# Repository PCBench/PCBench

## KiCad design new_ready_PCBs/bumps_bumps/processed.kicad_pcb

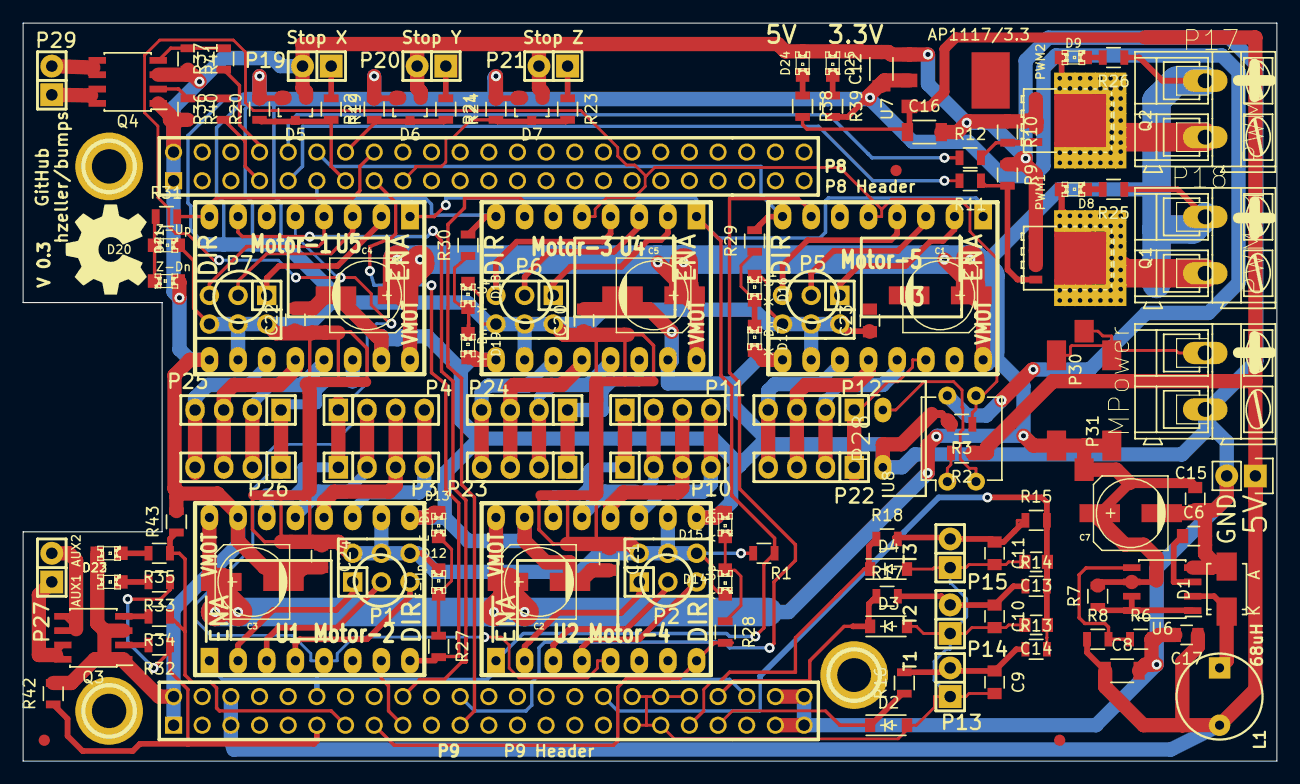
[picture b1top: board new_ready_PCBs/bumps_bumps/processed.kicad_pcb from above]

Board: 2 copper layers, 111.1 x 65.4 mm, 134 parts (0 on the bottom side), 101 nets.

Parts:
C1, C2, C3, C4, C5, C7: 100u; c_elec_6.3x7.7
C6: 110p; C_0805
C8: 100u; C_1206
C9, C10, C11, C14: 10u; C_0805
C12, C16: 22u; C_1206
C13, C15, C17, C20, C21, C22, C23, C24: 100n; C_0805
D1: STPS130A; Diode-SMA_Standard
D2, D3, D4: 1.8V; SOD-123
D5, D6, D7: BAT54S; SOT-23
D8: PWM1; LED-0805
D9: PWM2; LED-0805
D12: E-Up; LED-0805
D13: E-Dn; LED-0805
D14: A-Up; LED-0805
D15: A-Dn; LED-0805
D16: X-Up; LED-0805
D17: X-Dn; LED-0805
D18: Y-Up; LED-0805
D19: Y-Dn; LED-0805
D20: Z-Up; LED-0805
D21: Z-Dn; LED-0805
D22: AUX1; LED-0805
D23: AUX2; LED-0805
D24: 5V; LED-0805
D25: 3.3V; LED-0805
L1: 68uH; INDUCTOR_V
M1, M2, M3: CONN_1; 1pin
P1, P2, P5, P6, P7: DIL6; Pin_Header_Straight_2x03
P3, P4: Mot-E; Pin_Header_Straight_1x04
P8: P8 Header; PIN_ARRAY_23X2
P9: P9 Header; PIN_ARRAY_23X2
P10, P11: Mot-A; Pin_Header_Straight_1x04
P12, P22: Mot-X; Pin_Header_Straight_1x04
P13: T1; Pin_Header_Straight_1x02
P14: T2; Pin_Header_Straight_1x02
P15, P32: T3; Pin_Header_Straight_1x02
P16: MPower; AK300-2
P17: PWM-2; AK300-2
P18: PWM-1; AK300-2
P19: END-X; Pin_Header_Straight_1x02
P20: END-Y; Pin_Header_Straight_1x02
P21: END-Z; Pin_Header_Straight_1x02
P23, P24: Mot-Y; Pin_Header_Straight_1x04
P25, P26: Mot-Z; Pin_Header_Straight_1x04
P27: Aux; Pin_Header_Straight_1x02
P28: KillSwitch; WideHeader
P29: PWM; Pin_Header_Straight_1x02
P30, P31: CONN_01X01; FuseBlade
Q1, Q2: BUK9Y15-60E; SOT-669_LFPAK_ThermalVias-1
Q3, Q4: FDS9926A; SOIC-8_3.9x4.9mm_Pitch1.27mm
R1, R3, R13, R14, R15, R20, R22, R24: 4k7; R_0805
R2: 330; R_0805
R6, R27, R28, R29, R30, R31, R33, R35, R38, R39: 1k; R_0805
R7: 0R3; R_0805
R8: 3k; R_0805
R9, R10, R40, R41, R42, R43: 100k; R_0805
R11, R12, R16, R17, R18, R19, R21, R23, R32, R34, R36, R37: 68; R_0805
R25, R26: 2k2; R_0805
U1: Motor-2; POLOLU
U2: Motor-4; POLOLU
U3: Motor-5; POLOLU
U4: Motor-3; POLOLU
U5: Motor-1; POLOLU
U6: MC34063; SOIC-8_3.9x4.9mm_Pitch1.27mm
U7: AP1117/3.3; SOT-223-3
U8: PC817; DIP-4_W7.62mm

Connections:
AGND: C9.2, C10.2, C11.2, C13.2, C14.2, D2.2, D3.2, D4.2, P9.33, P9.34, P9.35, P9.36, P9.38, P13.1, P14.1, P15.1
AUX_1: P9.11, R32.1, R33.1, R42.1
AUX_2: P9.13, R34.1, R35.1, R43.1
DIR_A: P9.15, R28.2, U2.8
DIR_E: P8.15, R27.2, U1.8
DIR_X: P8.12, R29.2, U3.8
DIR_Y: P8.11, R30.2, U4.8
DIR_Z: P8.16, R31.2, U5.8
END_X: D5.3, P8.13, R19.2, R20.1
END_Y: D6.3, P8.14, R21.2, R22.1
END_Z: D7.3, P8.17, R23.2, R24.1
GND: C2.2, C3.2, C4.2, C5.2, C6.2, C7.2, C8.2, C12.2, C15.2, C16.2, C17.2, C20.2, C21.2, C22.2, C24.2, D1.2, D5.1, D6.1, D7.1, D13.1, D15.1, D17.1, D19.1, D21.1, D22.1, D23.1, D24.1, D25.1, P8.1, P8.2, P9.1, P9.2, P9.43, P9.44, P9.45, P9.46, P16.2, P19.2, P20.2, P21.2, P28.1, P32.2, Q1.1, Q1.2, Q1.3, Q2.1, Q2.2, Q2.3, Q3.1, Q3.3, Q4.1, Q4.3, R3.2, R6.2, R9.1, R10.1, R40.2, R41.2, R42.2, R43.2, U1.9, U1.15, U2.9, U2.15, U3.9, U4.9, U4.15, U5.9, U5.15, U6.4, U7.1
unnamed: C6.1, U6.3
unnamed: C9.1, P13.2, R13.1, R16.2
unnamed: C10.1, P14.2, R14.1, R17.2
unnamed: C11.1, P15.2, R15.1, R18.2
unnamed: D1.1, L1.1, U6.2
unnamed: D8.1, P18.2, Q1.5
unnamed: D8.2, R25.2
unnamed: D9.1, P17.2, Q2.5
unnamed: D9.2, R26.2
unnamed: D12.1, D13.2, R27.1
unnamed: D14.1, D15.2, R28.1
unnamed: D16.1, D17.2, R29.1
unnamed: D18.1, D19.2, R30.1
unnamed: D20.1, D21.2, R31.1
unnamed: D22.2, R33.2
unnamed: D23.2, R35.2
unnamed: D24.2, R38.1
unnamed: D25.2, R39.1
unnamed: P1.1, U1.2
unnamed: P1.2, U1.3
unnamed: P1.3, U1.4
unnamed: P2.1, U2.2
unnamed: P2.2, U2.3
unnamed: P2.3, U2.4
unnamed: P3.1, P4.1, U1.14
unnamed: P3.2, P4.2, U1.13
unnamed: P3.3, P4.3, U1.12
unnamed: P3.4, P4.4, U1.11
unnamed: P5.1, U3.2
unnamed: P5.2, U3.3
unnamed: P5.3, U3.4
unnamed: P6.1, U4.2
unnamed: P6.2, U4.3
unnamed: P6.3, U4.4
unnamed: P7.1, U5.2
unnamed: P7.2, U5.3
unnamed: P7.3, U5.4
unnamed: P10.1, P11.1, U2.14
unnamed: P10.2, P11.2, U2.13
unnamed: P10.3, P11.3, U2.12
unnamed: P10.4, P11.4, U2.11
unnamed: P12.1, P22.1, U3.14
unnamed: P12.2, P22.2, U3.13
unnamed: P12.3, P22.3, U3.12
unnamed: P12.4, P22.4, U3.11
unnamed: P16.1, P30.1
unnamed: P19.1, R19.1
unnamed: P20.1, R21.1
unnamed: P21.1, R23.1
unnamed: P23.1, P24.1, U4.14
unnamed: P23.2, P24.2, U4.13
unnamed: P23.3, P24.3, U4.12
unnamed: P23.4, P24.4, U4.11
unnamed: P25.1, P26.1, U5.14
unnamed: P25.2, P26.2, U5.13
unnamed: P25.3, P26.3, U5.12
unnamed: P25.4, P26.4, U5.11
unnamed: P27.1, Q3.7, Q3.8
unnamed: P27.2, Q3.5, Q3.6
unnamed: P28.2, U8.2
unnamed: P29.1, Q4.7, Q4.8
unnamed: P29.2, Q4.5, Q4.6
unnamed: Q1.4, R9.2, R11.1
unnamed: Q2.4, R10.2, R12.2
unnamed: Q3.2, R32.2
unnamed: Q3.4, R34.2
unnamed: Q4.2, R36.2, R40.1
unnamed: Q4.4, R37.2, R41.1
unnamed: R2.2, U8.1
unnamed: R6.1, R8.2, U6.5
unnamed: R7.1, U6.1, U6.7, U6.8
PWM_1: P8.9, R11.2
PWM_2: P8.10, R12.1
PWM_3: P8.7, R36.1
PWM_4: P8.8, R37.1
STEP_A: P9.42, U2.7
STEP_E: P9.17, U1.7
STEP_X: P9.22, U3.7
STEP_Y: P9.21, U4.7
STEP_Z: P9.18, U5.7
TEMP_1: D2.1, P9.39, R16.1
TEMP_2: D3.1, P9.40, R17.1
TEMP_3: D4.1, P9.37, R18.1
VDD_3V3: C12.1, C20.1, C21.1, C22.1, C23.1, C24.1, D5.2, D6.2, D7.2, D12.2, D14.2, D16.2, D18.2, D20.2, P1.4, P1.5, P1.6, P2.4, P2.5, P2.6, P5.4, P5.5, P5.6, P6.4, P6.5, P6.6, P7.4, P7.5, P7.6, R1.2, R20.2, R22.2, R24.2, R39.2, U1.10, U2.10, U3.10, U4.10, U5.10, U7.2, U8.4
VDD_5V: C8.1, C16.1, C17.1, L1.2, P9.5, P9.6, P32.1, R2.1, R8.1, R38.2, U7.3
VDD_ADC: C13.1, C14.1, P9.32, R13.2, R14.2, R15.2
VMOT: C1.1, C2.1, C3.1, C4.1, C5.1, C7.1, C15.1, P17.1, P18.1, P31.1, R7.2, R25.1, R26.1, U1.16, U2.16, U3.16, U4.16, U5.16, U6.6
~EN: P9.12, R1.1, U1.1, U2.1, U3.1, U4.1, U5.1
~EStop: R3.1, U1.5, U2.5, U3.5, U4.5, U5.5, U8.3

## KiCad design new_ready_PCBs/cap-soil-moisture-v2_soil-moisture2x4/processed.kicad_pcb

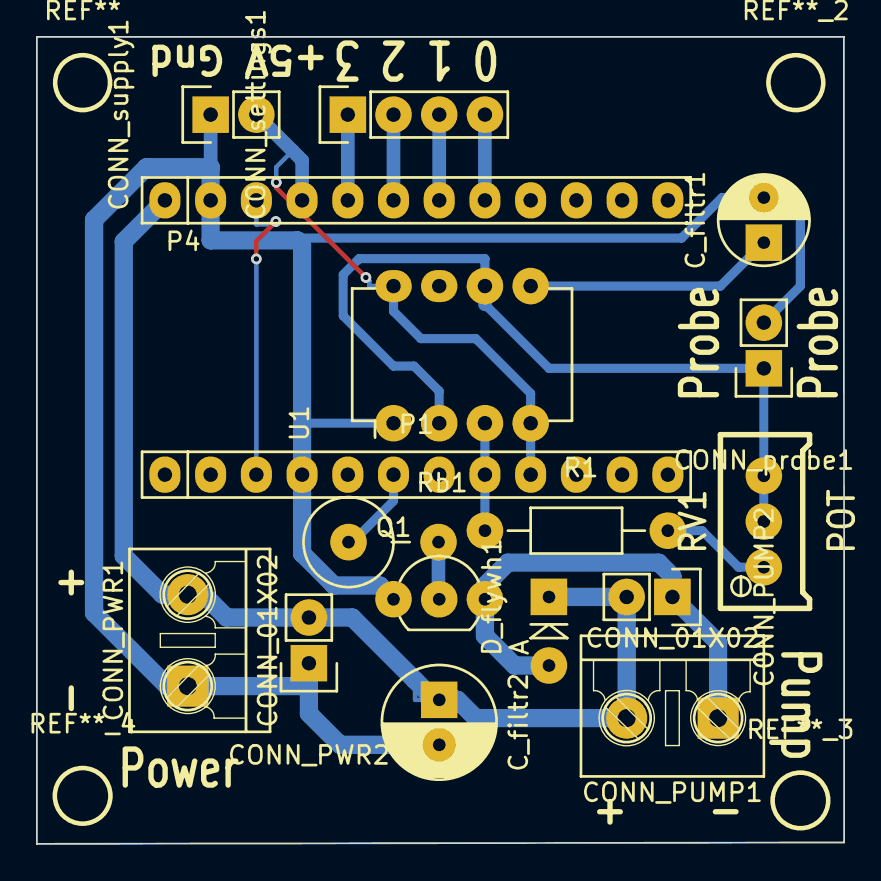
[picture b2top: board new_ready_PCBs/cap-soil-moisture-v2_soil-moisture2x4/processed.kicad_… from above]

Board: 2 copper layers, 44.8 x 44.8 mm, 17 parts (0 on the bottom side), 15 nets.

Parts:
CONN_PUMP1: CONN_01X02; KF301-2P-B
CONN_PUMP2: CONN_01X02; Pin_Header_Straight_1x02
CONN_PWR1: CONN_01X02; KF301-2P-B
CONN_PWR2: CONN_01X02; Pin_Header_Straight_1x02
CONN_probe1: CONN_01X02; Pin_Header_Straight_1x02
CONN_settings1: CONN_01X04; Pin_Header_Straight_1x04
CONN_supply1: CONN_01X02; Pin_Header_Straight_1x02
C_filtr1: CP1; C_Radial_D5_L6_P2.5
C_filtr2: CP1; C_Radial_D6.3_L11.2_P2.5
D_flywh1: D_Small; Diode_DO-41_SOD81_Vertical_AnodeUp
P1: Digital; Socket_Strip_Arduino_1x12
P4: Analog; Socket_Strip_Arduino_1x12
Q1: 2N2222; TO-92_Inline_Wide
R1: R; Resistor_Horizontal_RM10mm
RV1: POT; RV-bline
Rb1: 470R; Resistor_Vertical_RM5mm
U1: LM555N; DIP-8_W7.62mm

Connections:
+12V: CONN_PUMP1.2, CONN_PUMP2.2, CONN_PWR1.2, CONN_PWR2.2, C_filtr2.1, D_flywh1.1, P4.1
/3(**): P1.6, Rb1.1
/5(**): P1.8, R1.1, U1.3
/A0: CONN_settings1.4, P4.8
/A1: CONN_settings1.3, P4.7
/A2: CONN_settings1.2, P4.6
/A3: CONN_settings1.1, P4.5
/Reset: P1.3, P4.3
GND: CONN_PWR1.1, CONN_PWR2.1, CONN_probe1.2, CONN_supply1.1, C_filtr1.2, C_filtr2.2, P1.4, P4.2, Q1.1, U1.1
unnamed: CONN_PUMP1.1, CONN_PUMP2.1, D_flywh1.2, Q1.3
unnamed: CONN_probe1.1, RV1.2, RV1.3, U1.2, U1.6
unnamed: C_filtr1.1, U1.5
unnamed: Q1.2, Rb1.2
unnamed: R1.2, RV1.1
VCC: CONN_supply1.2, P1.9, P4.4, U1.4, U1.8

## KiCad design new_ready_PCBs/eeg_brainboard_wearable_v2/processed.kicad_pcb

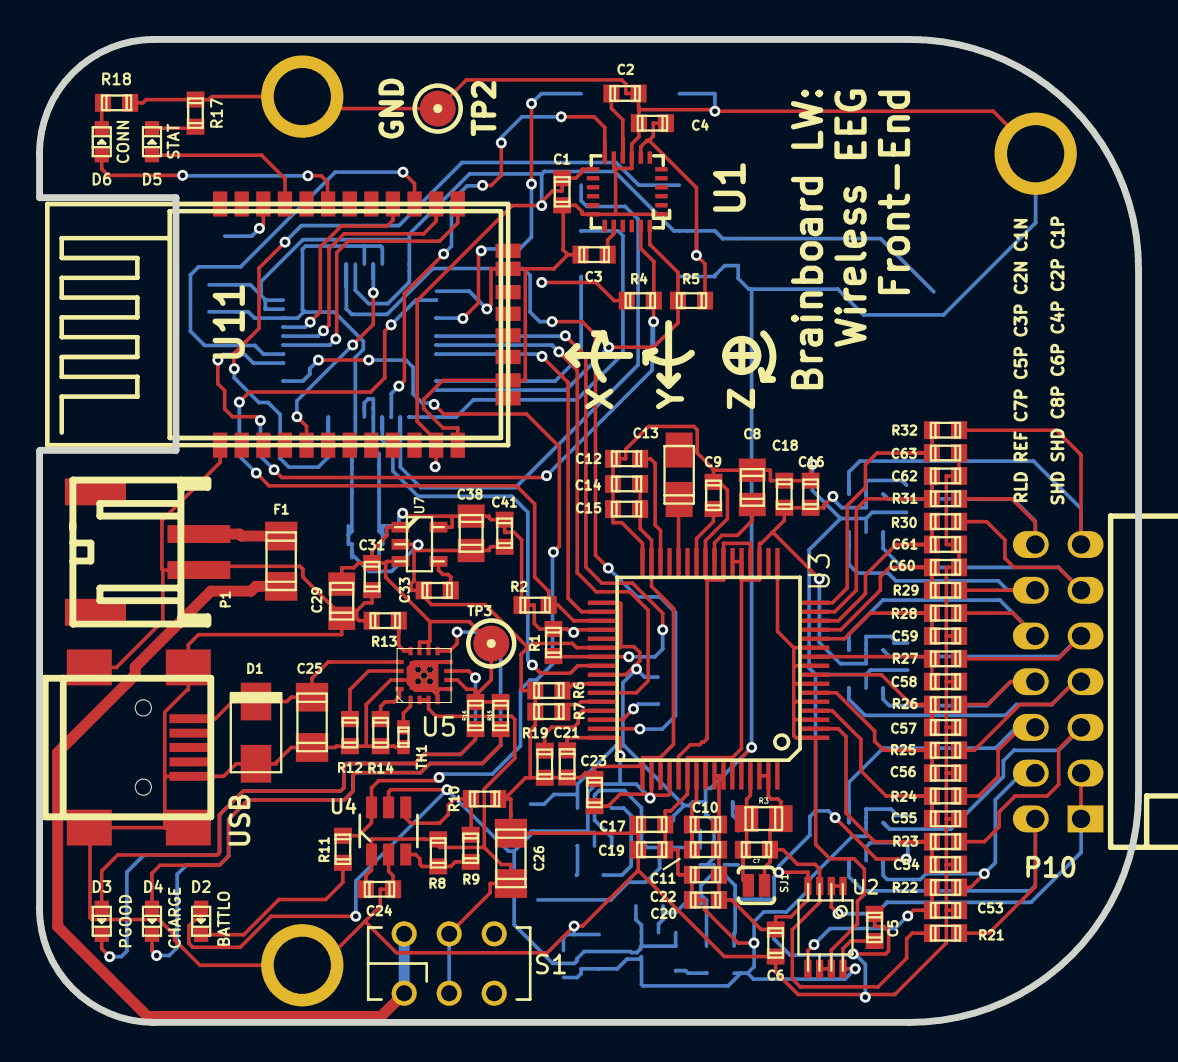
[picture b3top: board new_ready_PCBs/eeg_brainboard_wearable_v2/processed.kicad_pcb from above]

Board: 4 copper layers, 61.1 x 54.6 mm, 134 parts (0 on the bottom side), 89 nets.

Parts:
C1, C2, C5, C6, C11, C15, C18, C19, C22, C23, C24, C31, C42, C43, C45, C47, C48, C49, C50, C51, C52: 0.1uF; c_0603
C3: 2.2nF; c_0603
C4, C33, C34, C35: 0.01uF; c_0603
C7: 1nF; c_0603
C8, C29, C36, C37, C38, C46: 10uF; c_0805
C9, C10, C12, C14, C16, C17, C20, C21, C27, C28, C30, C32: 1uF; c_0603
C13: 100uF; c_tant_S
C25: 2.2uF; c_1206
C26: 10uF; c_1206
C39, C40, C41, C44: 2.2uF; c_0603
C53, C54, C55, C56, C57, C58, C59, C60, C61, C62, C63: 4.7nF; c_0603
CON1: USB; USB_MINI_B
D1: SMAJ7.0A; do214ac
D2: BATTLO; Led_0603
D3: PGOOD; Led_0603
D4: CHARGE; Led_0603
D5: STAT; Led_0603
D6: CONN; Led_0603
F1: PTC 500mA; r_1206
MTG1, MTG2, MTG3: MHOLE; BBB_MHOLE
P1: JST; s2b-ph-sm4-tb
P8: CONN_5X2; bb02-hp10
P10: CONN_14; pin_socket_7x2-90
R1, R2: 10K; r_0603
R3: 499K,0.1%; r_0805
R4, R5: 4.7k; r_0603
R6, R7, R19, R20: 10k; r_0603
R8: 562k; r_0603
R9: 51.1k; r_0603
R10: 383k; r_0603
R11, R15, R16, R17, R18: 2.2k; r_0603
R12: 52.3k; r_0603
R13: 1.18k; r_0603
R14: 4.42k; r_0603
R21, R22, R23, R24, R25, R26, R27, R28, R29, R30, R31, R32: 4.99K; r_0603
S1: DPDT; JS202011AQN
SJ1: NO BIAS FILT; SparkFun-Passives-SJ_2S-NO
TH1: NTC 10K; r_0402
TP1, TP2: GND; testpoint_2mm
TP3: PREREG; testpoint_2mm
TP4: -3V3; testpoint_2mm
TP5: +2V5; testpoint_2mm
TP6: -2V5; testpoint_2mm
TP7: BTRST; testpoint_2mm
TP8: 3V3; testpoint_2mm
U1: MPU6050; QFN24-4x4
U2: OPA2376; msoic-8
U3: ADS1299; TQFP_64
U4: LTC1998; tsot23-6
U5: BQ24074(T); s-pvqfn-n16-vias
U6: TPS60403; sot23-5
U7: TPS73233; sot23-5
U8: TPS73225; sot23-5
U9: TPS72325; sot23-5
U10: ATUC3L064; -TQFP48
U11: BLUETOOTH-RN42; roving_rn-42
U12, U13, U14: TPD4E001DBV; sot23-6

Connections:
+2.5V: C5.1, C16.1, C17.1, C18.1, C19.1, C20.1, C22.1, C36.1, C39.1, C42.1, C50.1, C51.1, C52.1, TP5.1, U2.8, U3.19, U3.21, U3.22, U3.54, U3.56, U3.59, U8.5, U12.5, U13.5, U14.5
+3.3V: C1.1, C4.1, C21.1, C23.1, C27.1, C32.1, C38.1, C41.1, C43.1, C44.1, C45.1, C46.1, C47.1, C48.1, C49.1, D2.1, P8.4, R1.1, R2.1, R4.1, R5.1, TP8.1, U1.8, U1.13, U3.36, U3.48, U3.50, U3.52, U4.5, U6.2, U7.5, U8.1, U8.3, U10.17, U10.18, U10.34, U10.35, U10.42, U10.48, U11.11
+BATT: C24.1, C26.1, R8.1, S1.2, S1.5, U4.1, U5.2, U5.3
-2.5V: C6.1, C8.1, C9.2, C10.2, C11.2, C12.2, C13.2, C14.1, C15.1, C16.2, C18.2, C20.2, C22.2, C37.1, C40.1, C42.2, C50.2, C51.2, C52.2, TP6.1, U2.4, U3.20, U3.23, U3.25, U3.32, U3.53, U3.57, U3.58, U9.5, U12.2, U13.2, U14.2
-3.3V: C30.1, TP4.1, U6.1, U9.2, U9.3
/BATTLO: R11.1, U4.6, U10.26
/Brainboard AFE/BIASINV: C7.1, R3.2, SJ1.1, U3.61
/Brainboard AFE/SRB1: U2.6, U2.7, U3.1, U3.3, U3.5, U3.7, U3.9, U3.11, U3.17
/Brainboard AFE/VCAP1: C13.1, U3.28
/Brainboard AFE/VCAP2: C12.1, U3.30
/Brainboard AFE/VCAP3: C10.1, C11.1, U3.55
/Brainboard AFE/VCAP4: C9.1, U3.26
/Brainboard AFE/VREFP: C8.2, U3.24
/Brainboard Analog In/BIAS_ELEC: P10.2, R21.1, U14.3
/Brainboard Analog In/CH1ELEC_N: P10.14, R31.1, U12.6
/Brainboard Analog In/CH1ELEC_P: P10.13, R32.1, U12.4
/Brainboard Analog In/CH2ELEC_N: P10.12, R29.1, U12.3
/Brainboard Analog In/CH2ELEC_P: P10.11, R30.1, U12.1
/Brainboard Analog In/CH3ELEC_P: P10.10, R28.1, U13.4
/Brainboard Analog In/CH4ELEC_P: P10.9, R27.1, U13.6
/Brainboard Analog In/CH5ELEC_P: P10.8, R26.1, U13.1
/Brainboard Analog In/CH6ELEC_P: P10.7, R25.1, U13.3
/Brainboard Analog In/CH7ELEC_P: P10.6, R24.1, U14.4
/Brainboard Analog In/CH8ELEC_P: P10.5, R23.1, U14.6
/Brainboard Analog In/REF_ELEC: P10.4, R22.1, U14.1
/Brainboard Bluetooth/FACTORY: TP7.1, U11.22
/Brainboard Bluetooth/STATUS: D6.1, U11.19
/Brainboard Bluetooth/STATUSn: D5.1, U11.21
/Brainboard IMU/CPOUT: C3.1, U1.20
/Brainboard IMU/REGOUT: C2.1, U1.10
/Brainboard MCU/RESET_MCU: P8.6, U10.22
/Brainboard MCU/TCK: P8.1, U10.11
/Brainboard MCU/TDI: P8.9, U10.4
/Brainboard MCU/TDO: P8.3, U10.13
/Brainboard MCU/TMS: P8.5, U10.14
/Brainboard Power/B+: F1.2, P1.1
/Brainboard Power/ILIM: R13.1, U5.12
/Brainboard Power/ISET: R14.1, U5.16
/Brainboard Power/OUT: C29.1, C31.1, R15.1, R16.1, TP3.1, U5.6, U5.10, U5.11, U7.1, U7.3
/Brainboard Power/TMR: R12.1, U5.14
/Brainboard Power/TS: TH1.1, U5.1
/Brainboard Power/VBUS: C25.1, CON1.1, D1.2, U5.13
/Brainboard Power/_B+: F1.1, S1.1, S1.4
/Brainboard Power/~CHG: D4.2, U5.9
/Brainboard Power/~PGOOD: D3.2, U5.7
/CS: R1.2, U3.39, U10.6
/DRDY: U3.47, U10.41
/PWDN: R2.2, U3.35, U10.2
AGND: C1.2, C2.2, C3.2, C4.2, C5.2, C6.2, C14.2, C15.2, C17.2, C19.2, C21.2, C23.2, C24.2, C25.2, C26.2, C27.2, C29.2, C30.2, C31.2, C32.2, C33.2, C34.2, C35.2, C36.2, C37.2, C38.2, C39.2, C40.2, C41.2, C43.2, C44.2, C45.2, C46.2, C47.2, C48.2, C49.2, C53.2, C54.2, C55.2, C56.2, C57.2, C58.2, C59.2, C60.2, C61.2, C62.2, C63.2, CON1.5, CON1.6, CON1.7, CON1.8, CON1.9, D1.1, MTG1.1, MTG2.1, MTG3.1, P1.2, P8.2, P8.10, R6.2, R7.2, R10.2, R12.2, R13.2, R14.2, R17.2, R18.2, R19.2, R20.2, TH1.2, TP1.1, TP2.1, U1.1, U1.9, U1.11, U1.18, U3.31, U3.33, U3.38, U3.41, U3.49, U3.51, U3.60, U4.2, U5.4, U5.5, U5.8, U5.15, U5.17, U6.4, U7.2, U8.2, U9.1, U10.1, U10.19, U10.33, U10.43, U10.45, U11.1, U11.12, U11.28, U11.29
AIN1N: C62.1, R31.2, U3.15
AIN1P: C63.1, R32.2, U3.16
AIN2N: C60.1, R29.2, U3.13
AIN2P: C61.1, R30.2, U3.14
AIN3P: C59.1, R28.2, U3.12
AIN4P: C58.1, R27.2, U3.10
AIN5P: C57.1, R26.2, U3.8
AIN6P: C56.1, R25.2, U3.6
AIN7P: C55.1, R24.2, U3.4
AIN8P: C54.1, R23.2, U3.2
BIAS: C7.2, R3.1, R21.2, SJ1.2, U2.3, U3.62, U3.63
IMU_INT: U1.12, U10.15
MISO: U3.43, U10.7
MOSI: U3.34, U10.8
unnamed: R20.1, U3.46
unnamed: R19.1, U3.45
unnamed: R7.1, U3.44
unnamed: R6.1, U3.42
unnamed: C33.1, U7.4
unnamed: D3.1, R16.2
unnamed: D4.1, R15.2
unnamed: R9.2, R10.1, U4.4
unnamed: R8.2, R9.1, U4.3
unnamed: D2.2, R11.2
unnamed: C28.2, U6.3
unnamed: C28.1, U6.5
unnamed: C34.1, U8.4
unnamed: C35.1, U9.4
unnamed: D6.2, R18.1
unnamed: D5.2, R17.1
REF_IN: C53.1, R22.2, U2.5
RESET_BT: U10.44, U11.5
SCL: R4.2, U1.23, U10.28
SCLK: U3.40, U10.16
SDA: R5.2, U1.24, U10.12
SHIELD: P10.1, P10.3, U2.1, U2.2
UARTBT_CTS: U10.29, U11.15
UARTBT_RTS: U10.32, U11.16
UARTBT_RX: U10.31, U11.14
UARTBT_TX: U10.30, U11.13

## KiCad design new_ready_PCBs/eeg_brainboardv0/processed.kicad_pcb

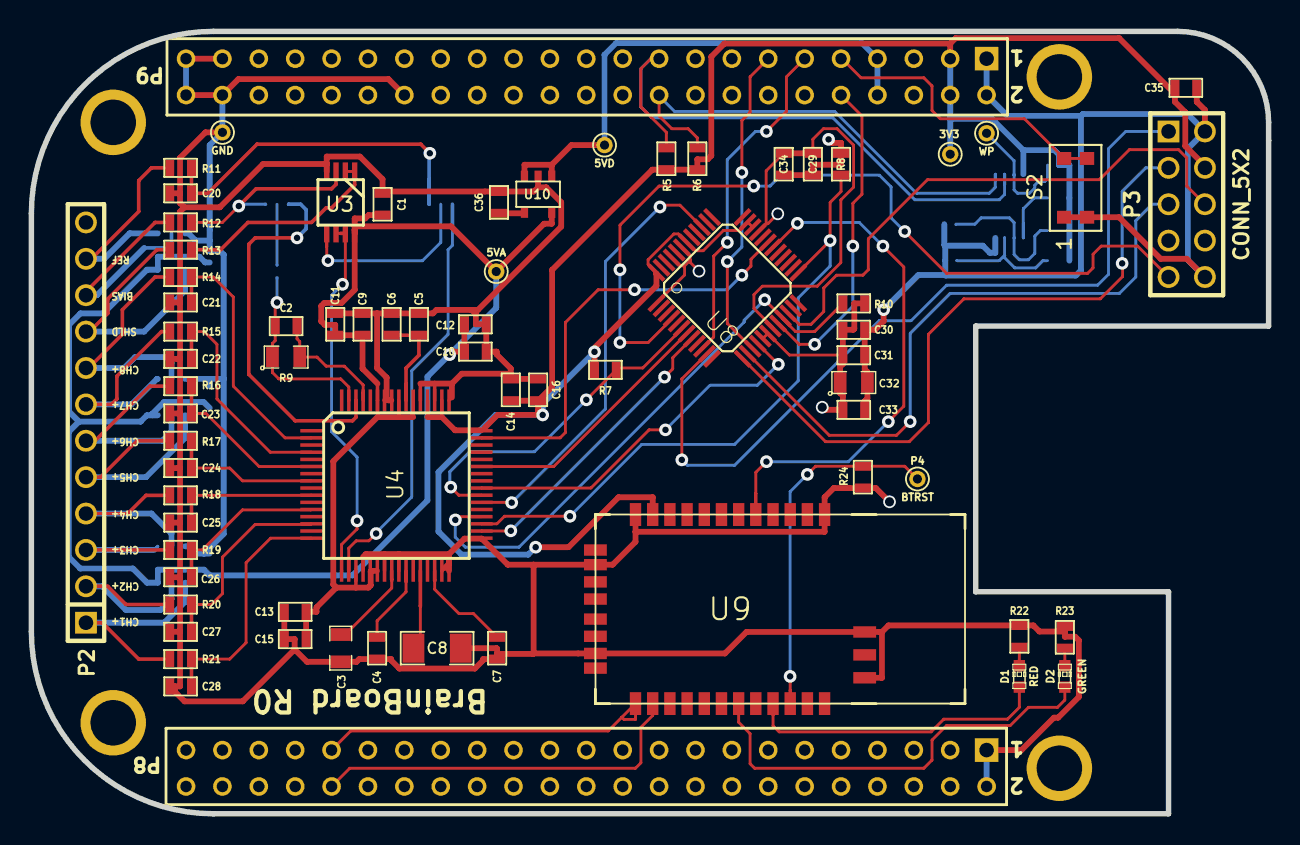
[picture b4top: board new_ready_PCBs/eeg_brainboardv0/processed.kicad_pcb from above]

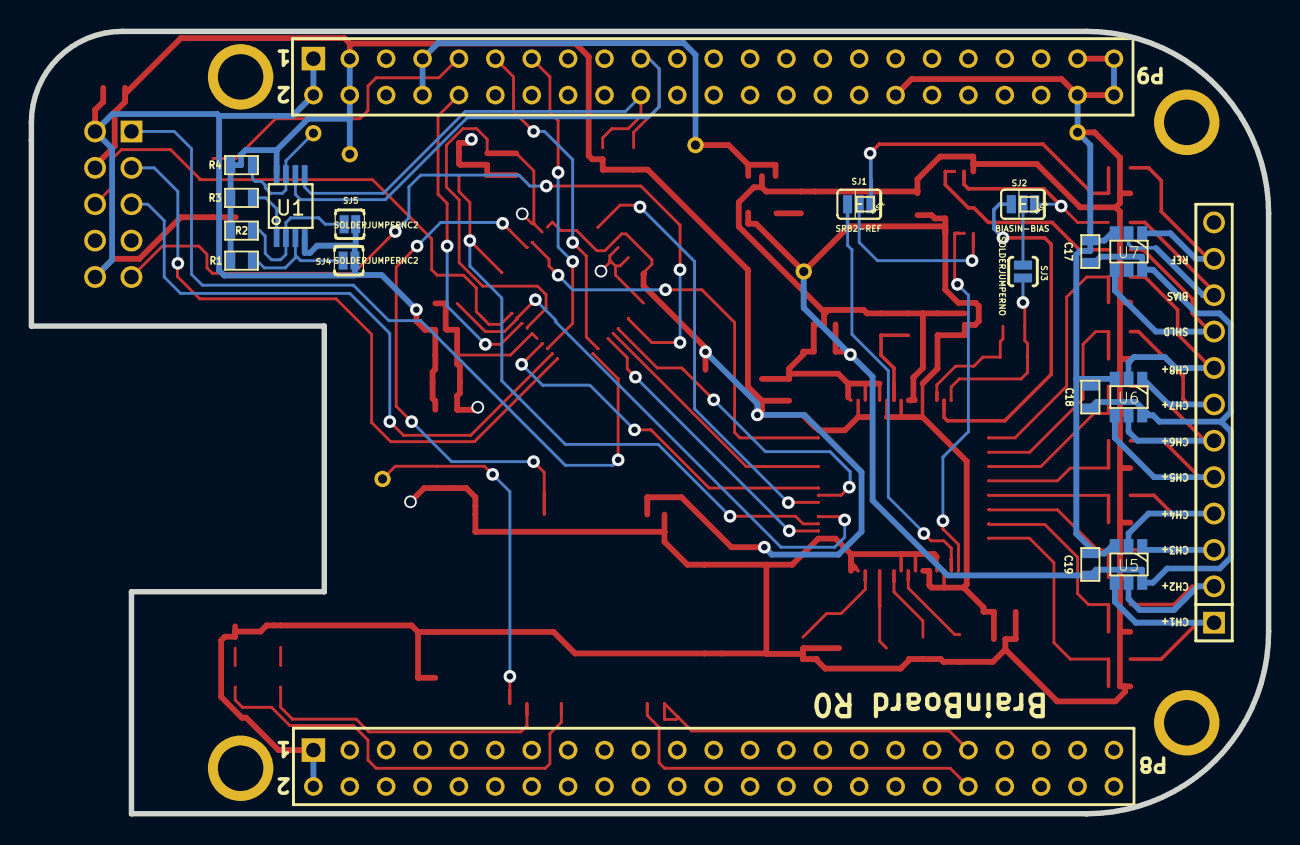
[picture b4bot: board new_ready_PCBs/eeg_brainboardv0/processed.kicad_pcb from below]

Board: 4 copper layers, 86.4 x 54.6 mm, 86 parts (16 on the bottom side), 70 nets.

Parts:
C1, C6, C11, C12, C15, C16, C17, C18, C19, C29, C31, C33, C34, C35, C36: 0.1uF; SM0603
C2: 1nF; SM0603
C3, C32: 10uF; SM0805
C4, C5, C7, C9, C10, C13, C14: 1uF; SM0603
C8: 100uF; SM1206
C20, C21, C22, C23, C24, C25, C26, C27, C28: 4.7nF; SM0603
C30: 2.2uF; SM0603
D1: RED; LED-0603
D2: GREEN; LED-0603
P1: WP; PINTST
P2: CONN_12; PIN_ARRAY-12X1
P3: CONN_5X2; PIN_ARRAY_5x2
P4: BTRST; PINTST
P5: GND; PINTST
P6: 5VD; PINTST
P7: 3V3; PINTST
P8: 5VA; PINTST
R1, R2, R3: 4.7K; SM0603
R4, R7, R8, R10, R24: 10K; SM0603
R5, R6: 5.6K; SM0603
R9: 499K,0.1%; SM0805
R11, R12, R13, R14, R15, R16, R17, R18, R19, R20, R21: 4.99K; SM0603
R22, R23: 330; SM0603
S2: SMT_BUTTON; KMR231GLFS
SJ1, SJ2: SOLDERJUMPER_2WAYPASTE2&3; SparkFun-Passives-SJ_3_PASTE2&3
SJ3: SOLDERJUMPERNO; SparkFun-Passives-SJ_2S-NO
SJ4, SJ5: SOLDERJUMPERNC2; SparkFun-Passives-SJ_2S-NOTRACE
U1: 24C256; SSOP8
U2: BEAGLEBONE_BLACK
U3: OPA2376; MSOP_8
U4: ADS1299; TQFP_64
U5, U6, U7: TPD4E001; SOT23_6
U8: ATUC3L064; -TQFP48
U9: BLUETOOTH-RN42; SparkFun-RF-RN41
U10: TPS73150; SOT23-5

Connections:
3V3: C14.1, C16.1, C29.1, C30.1, C31.1, C32.1, C33.1, C34.1, C35.1, P3.4, P7.1, R1.1, R2.1, R3.1, R4.1, R5.1, R6.1, R7.1, R8.1, R10.1, U1.8, U2.B3, U2.B4, U4.48, U4.50, U4.52, U8.17, U8.18, U8.34, U8.35, U8.42, U8.48, U9.11
+5VA: C1.1, C9.1, C10.1, C11.1, C12.1, C13.1, C15.1, C17.1, C18.1, C19.1, P8.1, U3.8, U4.19, U4.21, U4.22, U4.54, U4.56, U4.59, U5.6, U6.6, U7.6, U10.5
+5VD: P6.1, U2.B7, U2.B8, U10.1, U10.3
/A0: R3.2, U1.1
/A1: R2.2, SJ5.1, U1.2
/A2: R1.2, SJ4.1, U1.3
/BrainBoard AFE/BIASIN: SJ2.1, U4.62
/BrainBoard AFE/BIASINV: C2.1, R9.2, U4.61
/BrainBoard AFE/BIASOUT: C2.2, R9.1, SJ3.2, U4.63
/BrainBoard AFE/SRB1: U3.6, U3.7, U4.17
/BrainBoard AFE/SRB2: SJ1.1, U4.18
/BrainBoard AFE/VCAP1: C8.1, U4.28
/BrainBoard AFE/VCAP2: C7.1, U4.30
/BrainBoard AFE/VCAP3: C5.1, C6.1, U4.55
/BrainBoard AFE/VCAP4: C4.1, U4.26
/BrainBoard AFE/VREFP: C3.2, U4.24
/BrainBoard Analog In/BIAS_ELEC: P2.10, R12.1, U7.2
/BrainBoard Analog In/BIAS_SHD: P2.9, R13.1, U7.4
/BrainBoard Analog In/CH1ELEC_P: P2.1, R21.1, U5.4
/BrainBoard Analog In/CH2ELEC_P: P2.2, R20.1, U5.5
/BrainBoard Analog In/CH3ELEC_P: P2.3, R19.1, U5.1
/BrainBoard Analog In/CH4ELEC_P: P2.4, R18.1, U5.2
/BrainBoard Analog In/CH5ELEC_P: P2.5, R17.1, U6.4
/BrainBoard Analog In/CH6ELEC_P: P2.6, R16.1, U6.5
/BrainBoard Analog In/CH7ELEC_P: P2.7, R15.1, U6.1
/BrainBoard Analog In/CH8ELEC_P: P2.8, R14.1, U6.2
/BrainBoard Analog In/REF_ELEC: P2.11, R11.1, U7.1
/BrainBoard Bluetooth/FACTORY: P4.1, R24.1, U9.22
/BrainBoard Bluetooth/STATUS: D2.1, U9.19
/BrainBoard Bluetooth/STATUSn: D1.1, U9.21
/BrainBoard MCU/RESET_MCU: P3.6, U8.22
/BrainBoard MCU/TCK: P3.1, U8.11
/BrainBoard MCU/TDI: P3.9, U8.4
/BrainBoard MCU/TDO: P3.3, U8.13
/BrainBoard MCU/TMS: P3.5, U8.14
/CS: R7.2, U4.39, U8.6
/DRDY: U4.47, U8.31
/PWDN: R8.2, U4.35, U8.25
/RESET: R10.2, U4.36, U8.21
/SCL: R5.2, U1.6, U2.B19
/SDA: R6.2, U1.5, U2.B20
/WP: P1.1, R4.2, U1.7
AGND: C1.2, C3.1, C4.2, C5.2, C6.2, C7.2, C8.2, C9.2, C10.2, C11.2, C12.2, C13.2, C14.2, C15.2, C16.2, C17.2, C18.2, C19.2, C20.2, C21.2, C22.2, C23.2, C24.2, C25.2, C26.2, C27.2, C28.2, C29.2, C30.2, C31.2, C32.2, C33.2, C34.2, C35.2, C36.2, P3.2, P3.10, P5.1, R22.2, R23.2, R24.2, S2.1, S2.3, SJ4.2, SJ5.2, U1.4, U2.A1, U2.A2, U2.B1, U2.B2, U2.B34, U2.B43, U2.B44, U2.B45, U2.B46, U3.4, U4.20, U4.23, U4.25, U4.31, U4.32, U4.33, U4.49, U4.51, U4.53, U4.57, U4.58, U5.3, U6.3, U7.3, U8.1, U8.19, U8.33, U8.43, U8.45, U9.1, U9.12, U9.25, U9.27, U9.28, U9.29, U10.2
AIN1P: C28.1, R21.2, U4.16
AIN2P: C27.1, R20.2, U4.14
AIN3P: C26.1, R19.2, U4.12
AIN4P: C25.1, R18.2, U4.10
AIN5P: C24.1, R17.2, U4.8
AIN6P: C23.1, R16.2, U4.6
AIN7P: C22.1, R15.2, U4.4
AIN8P: C21.1, R14.2, U4.2
BIAS: R12.2, SJ2.3, U3.3
MISO: U4.43, U8.7
MOSI: U4.34, U8.8
unnamed: S2.2, S2.4, U2.B9
unnamed: SJ2.2, SJ3.1
unnamed: SJ1.2, U3.5
unnamed: D2.2, R23.1
unnamed: D1.2, R22.1
unnamed: C36.1, U10.4
REF: C20.1, R11.2, SJ1.3
RESET_BT: U8.30, U9.5
SCLK: U4.40, U8.16
SHIELD: R13.2, U3.1, U3.2
START: U4.38, U8.39
SYS_RESETn: U2.B10, U8.20
UARTBT_RX: U2.A37, U9.13
UARTBT_TX: U2.A38, U9.14
UARTUC_RX: U2.B13, U8.15
UARTUC_TX: U2.B11, U8.10

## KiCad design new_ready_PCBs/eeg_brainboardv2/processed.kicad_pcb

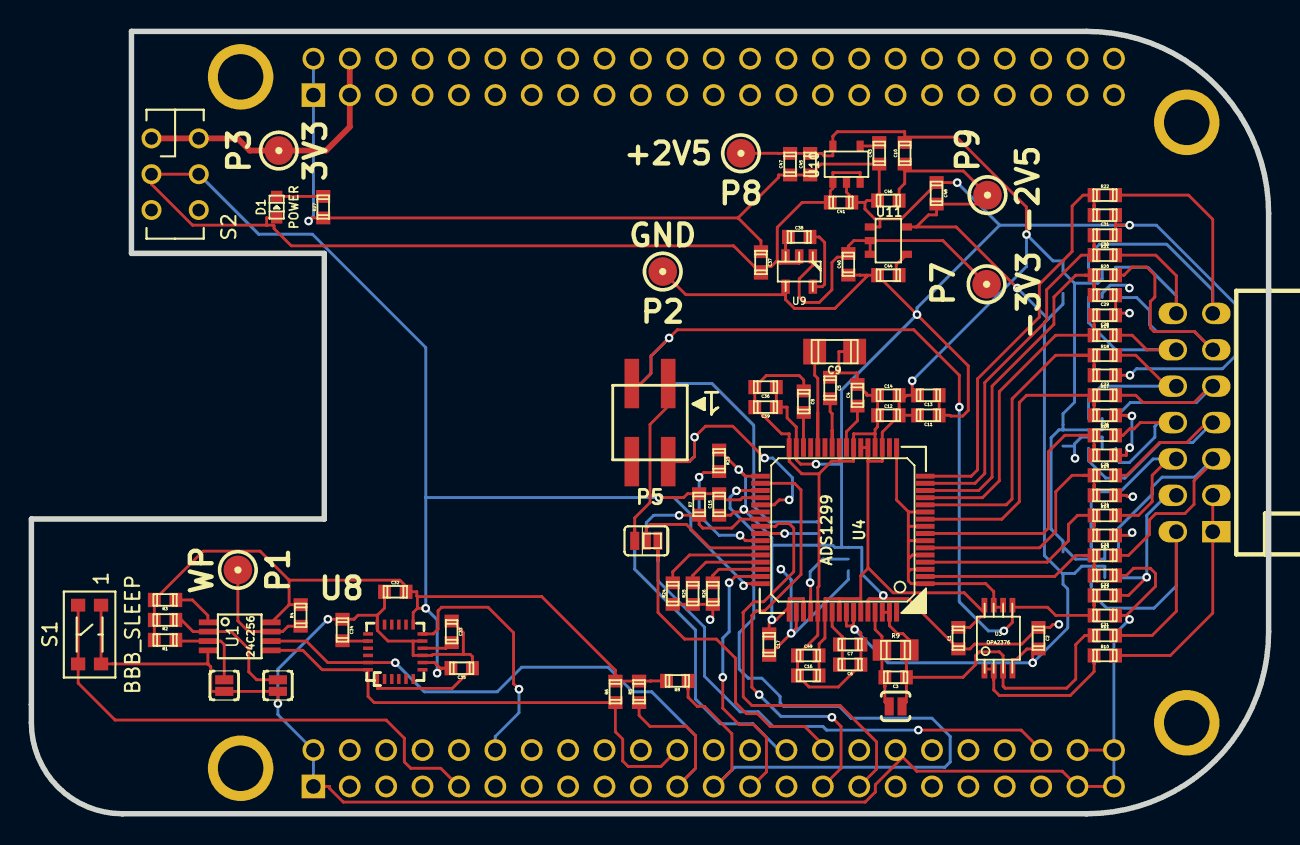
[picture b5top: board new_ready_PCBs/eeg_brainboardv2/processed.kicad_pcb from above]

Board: 4 copper layers, 86.4 x 54.6 mm, 105 parts (0 on the bottom side), 72 nets.

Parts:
C1, C2, C7, C12, C13, C16, C17, C18, C19, C20, C32, C33, C39, C49: 0.1uF; c_0603
C3: 1nF; c_0603
C4, C45, C46: 10uF; c_0603
C5, C6, C8, C10, C11, C14, C15, C36, C37, C38, C40, C41: 1uF; c_0603
C9: 100uF; c_1206
C21, C22, C23, C24, C25, C26, C27, C28, C29, C30, C31: 4.7nF; c_0603
C34: 2.2nF; c_0603
C35, C43, C44: 0.01uF; c_0603
C47, C48: 2.2uF; c_0603
D1: POWER; Led_0603
P1: WP; testpoint_2mm
P2: GND; testpoint_2mm
P3: 3V3; testpoint_2mm
P4: DAISY_IN_CONN; bb02-hp04
P5: DAISY_OUT_CONN; bb02-hp04
P6: CONN_14; pin_socket_7x2-90
P7: -3V3; testpoint_2mm
P8: +2V5; testpoint_2mm
P9: -2V5; testpoint_2mm
R1, R2, R3: 4.7K; r_0603
R4, R7, R8, R23, R24, R25, R26: 10K; r_0603
R5, R6: 5.6K; r_0603
R9: 499K,0.1%; r_0805
R10, R11, R12, R13, R14, R15, R16, R17, R18, R19, R20, R21, R22: 4.99K; r_0603
R27: 330; r_0603
S1: BBB_SLEEP; KMR231GLFS
S2: DPDT; JS202011AQN
SJ1: A2; SparkFun-Passives-SJ_2S-NOTRACE
SJ2: A1; SparkFun-Passives-SJ_2S-NOTRACE
SJ3, SJ6: DAISY_CS; SparkFun-Passives-SJ_3_PASTE2&3
SJ4: DAISY_OUT; SparkFun-Passives-SJ_3_PASTE2&3
SJ5: NO BIAS FILT; SparkFun-Passives-SJ_2S-NO
SJ7: CLKSEL; SparkFun-Passives-SJ_3_PASTE1&2
U1: 24C256; SSOP-8
U2: BEAGLEBONE_BLACK
U3: OPA2376; msoic-8
U4: ADS1299; lqfp64
U5, U6, U7: TPD4E001DBV; sot23-6
U8: MPU6050; QFN24-4x4
U9: TPS60403; sot23-5
U10: TPS73225; SOT23-5
U11: TPS72325; SOT23-5

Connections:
+2.5V: C1.1, C10.1, C11.1, C12.1, C13.1, C14.1, C16.1, C18.1, C19.1, C20.1, C45.1, C47.1, C49.1, P8.1, U3.8, U4.19, U4.21, U4.22, U4.54, U4.56, U4.59, U5.5, U6.5, U7.5, U10.5
+3.3V: C15.1, C17.1, C32.1, C35.1, C37.1, C41.1, D1.1, R1.1, R2.1, R3.1, R4.1, R5.1, R6.1, R7.1, R8.1, S2.2, S2.5, SJ7.1, U1.8, U4.36, U4.48, U4.50, U8.8, U8.13, U9.2, U10.1, U10.3
-2.5V: C2.1, C4.1, C5.2, C6.2, C7.2, C8.2, C9.2, C10.2, C12.2, C14.2, C16.2, C18.2, C19.2, C20.2, C36.1, C39.1, C46.1, C48.1, C49.2, P9.1, U3.4, U4.20, U4.23, U4.25, U4.32, U4.53, U4.57, U4.58, U5.2, U6.2, U7.2, U11.5
-3.3V: C40.1, P7.1, U9.1, U11.2, U11.3
/A0: R3.2, U1.1
/A1: R2.2, SJ2.1, U1.2
/A2: R1.2, SJ1.1, U1.3
/Brainboard AFE//CS: R7.2, SJ3.2, U4.39
/Brainboard AFE/BIASINV: C3.1, R9.2, SJ5.1, U4.61
/Brainboard AFE/CLKSEL: SJ7.2, U4.52
/Brainboard AFE/DAISY: SJ6.2, U4.41
/Brainboard AFE/DAISY_IN: P4.2, SJ6.1
/Brainboard AFE/DOUT: SJ4.2, U4.43
/Brainboard AFE/SRB1: U3.6, U3.7, U4.1, U4.3, U4.5, U4.7, U4.9, U4.11, U4.17
/Brainboard AFE/VCAP1: C9.1, U4.28
/Brainboard AFE/VCAP2: C8.1, U4.30
/Brainboard AFE/VCAP3: C6.1, C7.1, U4.55
/Brainboard AFE/VCAP4: C5.1, U4.26
/Brainboard AFE/VREFP: C4.2, U4.24
/Brainboard Analog In/BIAS_ELEC: P6.2, R11.1, U7.3
/Brainboard Analog In/BIAS_SHD: P6.1, P6.3, R10.1
/Brainboard Analog In/CH1ELEC_N: P6.14, R21.1, U5.6
/Brainboard Analog In/CH1ELEC_P: P6.13, R22.1, U5.4
/Brainboard Analog In/CH2ELEC_N: P6.12, R19.1, U5.3
/Brainboard Analog In/CH2ELEC_P: P6.11, R20.1, U5.1
/Brainboard Analog In/CH3ELEC_P: P6.10, R18.1, U6.4
/Brainboard Analog In/CH4ELEC_P: P6.9, R17.1, U6.6
/Brainboard Analog In/CH5ELEC_P: P6.8, R16.1, U6.1
/Brainboard Analog In/CH6ELEC_P: P6.7, R15.1, U6.3
/Brainboard Analog In/CH7ELEC_P: P6.6, R14.1, U7.4
/Brainboard Analog In/CH8ELEC_P: P6.5, R13.1, U7.6
/Brainboard Analog In/REF_ELEC: P6.4, R12.1, U7.1
/Brainboard IMU/CPOUT: C34.1, U8.20
/Brainboard IMU/REGOUT: C33.1, U8.10
/CS_DAISY: SJ3.1, U2.B42
/CS_MAIN: SJ3.3, U2.B28
/DRDY: U2.B25, U4.47
/PWDN: R8.2, U2.B23, U4.35
/WP: P1.1, R4.2, U1.7
AGND: C1.2, C2.2, C11.2, C13.2, C15.2, C17.2, C21.2, C22.2, C23.2, C24.2, C25.2, C26.2, C27.2, C28.2, C29.2, C30.2, C31.2, C32.2, C33.2, C34.2, C35.2, C36.2, C37.2, C39.2, C40.2, C41.2, C43.2, C44.2, C45.2, C46.2, C47.2, C48.2, P2.1, R23.2, R24.2, R25.2, R26.2, R27.2, S1.1, S1.3, SJ1.2, SJ2.2, SJ6.3, SJ7.3, U1.4, U2.A1, U2.A2, U2.B1, U2.B2, U2.B34, U2.B43, U2.B44, U2.B45, U2.B46, U4.31, U4.33, U4.38, U4.49, U4.51, U4.60, U8.1, U8.9, U8.11, U8.18, U9.4, U10.2, U11.1
AIN1N: C30.1, R21.2, U4.15
AIN1P: C31.1, R22.2, U4.16
AIN2N: C28.1, R19.2, U4.13
AIN2P: C29.1, R20.2, U4.14
AIN3P: C27.1, R18.2, U4.12
AIN4P: C26.1, R17.2, U4.10
AIN5P: C25.1, R16.2, U4.8
AIN6P: C24.1, R15.2, U4.6
AIN7P: C23.1, R14.2, U4.4
AIN8P: C22.1, R13.2, U4.2
BIAS: C3.2, R9.1, R11.2, SJ5.2, U3.3, U4.62, U4.63
CLK: P4.1, P5.2, U4.37
DAISY_OUT: P5.1, SJ4.1
I2C2_SCL: R5.2, U1.6, U2.B21, U8.23
I2C2_SDA: R6.2, U1.5, U2.B22, U8.24
IMU_INT: U2.B12, U8.12
MISO: SJ4.3, U2.B30
MOSI: U2.B29, U4.34
unnamed: S1.2, S1.4, U2.B9
unnamed: R23.1, U4.42
unnamed: R24.1, U4.44
unnamed: R25.1, U4.45
unnamed: R26.1, U4.46
unnamed: C44.1, U11.4
unnamed: C43.1, U10.4
unnamed: D1.2, R27.1
unnamed: C38.1, U9.5
unnamed: C38.2, U9.3
REF_IN: C21.1, P4.4, P5.3, R12.2, U3.5
SCLK: U2.B31, U4.40
SHIELD: R10.2, U3.1, U3.2
VCC: P3.1, S2.1, S2.4, U2.A3, U2.A4

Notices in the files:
new_ready_PCBs/bumps_bumps/processed.kicad_pcb:
License: CC-BY-SA
